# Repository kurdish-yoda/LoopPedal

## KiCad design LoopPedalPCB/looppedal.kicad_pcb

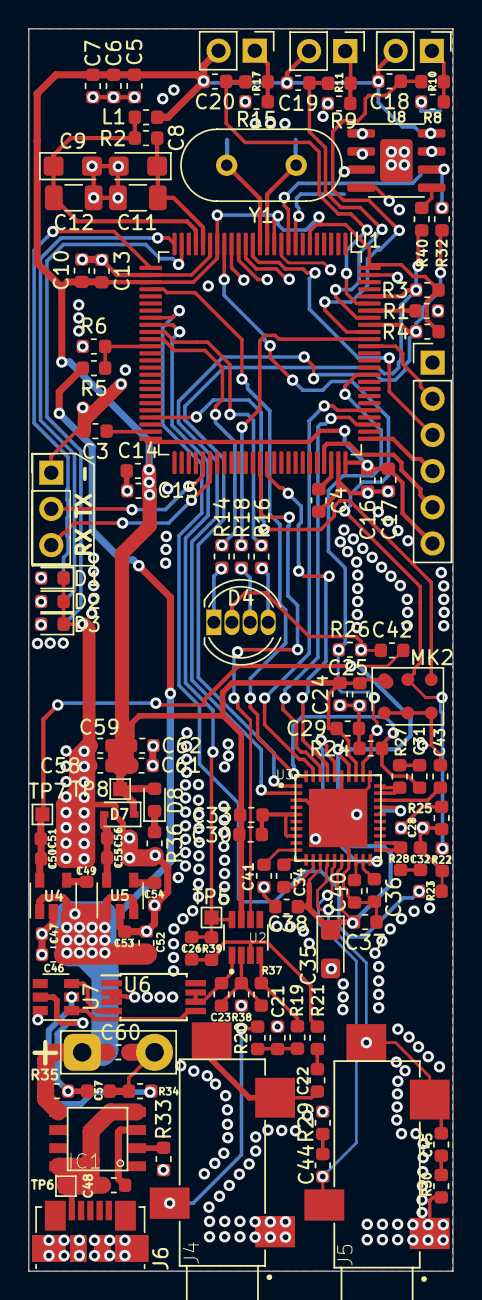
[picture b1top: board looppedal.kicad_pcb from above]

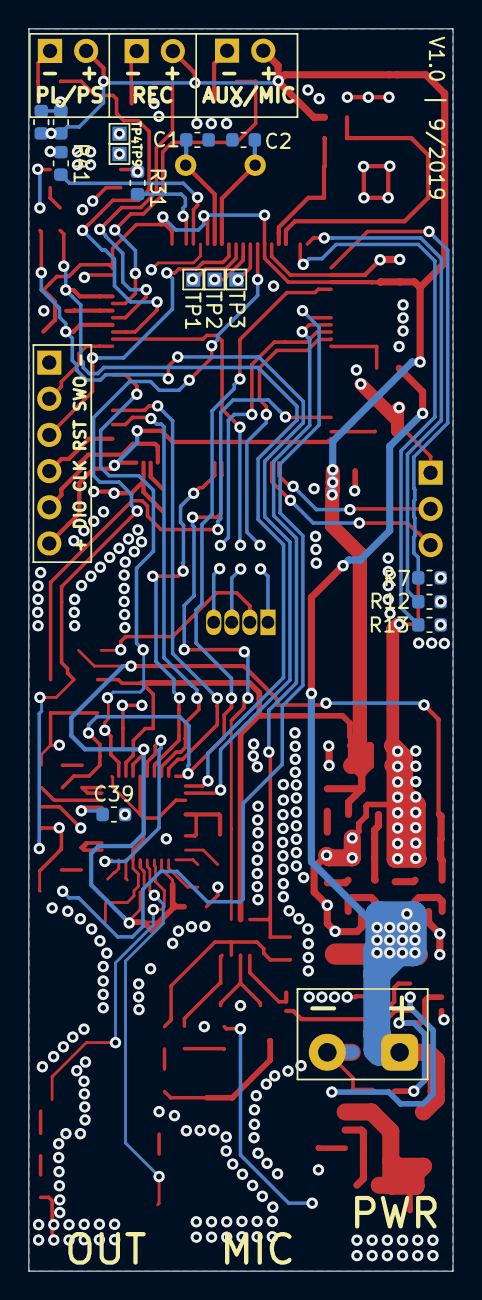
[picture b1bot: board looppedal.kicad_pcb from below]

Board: 2 copper layers, 29.8 x 87.2 mm, 140 parts (15 on the bottom side), 94 nets.

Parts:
+: Battery; TestPoint_2Pads_Pitch5.08mm_Drill1.3mm
C1, C2: 20pF; C_0603_1608Metric
C3, C4: 2.2uF; C_0603_1608Metric
C5, C6, C7, C10, C13, C14, C15, C16, C18, C19, C20, C24, C27, C28, C47, C51, C53, C56, C58, C59, C61, C62, C63: 100nF; C_0603_1608Metric
C8, C9: 1uF; CP_EIA-3216-12_Kemet-S
C11, C12: 100nF; C_1206_3216Metric
C17, C30, C31, C32, C33, C34, C36, C40, C41, C46, C50, C52, C55: 1uF; C_0603_1608Metric
C21, C25, C60: 10uF; C_0603_1608Metric
C22, C29, C37, C38, C42: 0.1uF; C_0603_1608Metric
C23: 0.01uF; C_0603_1608Metric
C26: 47pF; C_0603_1608Metric
C35: CP; CP_EIA-3216-12_Kemet-S
C39, C43: 150pF; C_0603_1608Metric
C44, C45: 0.022uF; C_0603_1608Metric
C48, C57: 0.1uF/25V; C_0603_1608Metric
C49, C54: 10nF; C_0603_1608Metric
D1, D2, D3, D8: LED; LED_0603_1608Metric
D4: LED_RCBG; LED_D5.0mm-4_RGB
D7: D_Schottky_ALT; D_SOD-323
IC1: TP4056; SOP-8
J1: SW_PLAY_PAUSE; PinHeader_1x02_P2.54mm_Vertical
J2: SW_REC; PinHeader_1x02_P2.54mm_Vertical
J3: SW_AUX_MIC; PinHeader_1x02_P2.54mm_Vertical
J4, J5: SJ-3524-SMT-PI; CUI_SJ-3524-SMT-PI
J6: USB_B_Micro; USB_Micro-B_Molex_47346-0001
J8: Conn_01x06; PinHeader_1x06_P2.54mm_Vertical
J9: DBG; PinHeader_1x03_P2.54mm_Vertical
L1: fcm; L_0603_1608Metric
MK2: MP45DT02; ST_HLGA-6_3.76x4.72mm_P1.65mm
R1, R6: 510; R_0603_1608Metric
R2: 47; R_0603_1608Metric
R3, R4: 4.7k; R_0603_1608Metric
R5: 10k; R_0603_1608Metric
R7, R12, R13, R14, R16, R18, R19, R31, R34, R36, R41: 1K; R_0603_1608Metric
R8, R9, R15, R24, R25, R37, R38: 100K; R_0603_1608Metric
R10, R11, R17, R26: 10K; R_0603_1608Metric
R20: 2K2; R_0603_1608Metric
R21: 20K; R_0603_1608Metric
R22, R33: 1.2K; R_0603_1608Metric
R23, R32, R40: 0; R_0603_1608Metric
R27, R28, R35: 100; R_0603_1608Metric
R29, R30: 51; R_0603_1608Metric
R39: 200K; R_0603_1608Metric
TP1, TP2, TP3, TP4, TP5, TP6, TP7, TP8, TP9: TestPoint; TestPoint_Pad_1.0x1.0mm
U1: STM32F407VGTx; LQFP-100_14x14mm_P0.5mm
U2: MAX4468EKAT; SOT65P280X145-8N
U3: CS43L22-CNZ; QFN50P600X600X100-41N
U4: LD3985M25R_SOT23; SOT-23-5
U5: LD3985M33R_SOT23; SOT-23-5
U6: FS8205; TSSOP-8_4.4x3mm_P0.65mm
U7: DW01; SOT-23-6
U8: M24M02-DRMN6TP; SOIC-8-1EP_3.9x4.9mm_P1.27mm_EP2.29x3mm
Y1: 8MHz; Crystal_HC49-U_Vertical

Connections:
+2V5: C35.1, C37.2, C38.2, C42.2, C50.1, C51.1, TP7.1, U3.13, U3.16, U3.34, U4.5
-BATT: +.2, C1.2, C2.2, C3.2, C4.2, C5.1, C6.1, C7.1, C8.2, C9.2, C10.1, C11.1, C12.2, C13.1, C14.1, C15.1, C16.1, C17.1, C21.1, C23.2, C24.2, C25.2, C27.1, C28.1, C29.1, C35.2, C36.2, C37.1, C38.1, C39.2, C40.2, C41.2, C42.1, C43.2, C46.2, C47.2, C48.2, C49.2, C50.2, C51.2, C52.2, C53.2, C54.2, C55.2, C56.2, C57.1, C58.2, C59.2, C60.2, C61.2, C62.2, C63.1, D1.1, D2.1, D3.1, D4.2, IC1.1, IC1.3, J4.1, J5.1, J6.5, J6.6, J8.1, J9.1, MK2.1, MK2.2, MK2.3, R1.2, R6.1, R8.1, R9.1, R15.1, R24.1, R25.2, R26.2, R29.1, R30.1, R33.1, R34.2, R36.2, R38.1, U1.10, U1.20, U1.27, U1.74, U1.99, U2.1, U3.3, U3.17, U3.31, U3.35, U3.41, U4.2, U5.2, U6.2, U6.3, U6.6, U6.7, U7.6, U8.4, U8.9
BAT_VCC: +.1, C46.1, C47.1, C52.1, C53.1, C60.1, IC1.5, R5.2, R35.1, U4.1, U4.3, U5.1, U5.3
CHRG_0: R7.2, U1.26
CHRG_1: R12.2, U1.25
CHRG_2: R13.2, U1.24
MCU_NRST: J8.3, U1.14
MCU_VBAT: C5.2, C6.2, C7.2, C10.2, C13.2, C14.2, C15.2, C16.2, C17.2, C18.2, C19.2, C20.2, C24.1, C25.1, C27.2, C29.2, C30.1, C33.1, C58.1, C59.1, C61.1, C62.1, C63.2, D7.1, D8.2, J1.2, J2.2, J3.2, J8.6, L1.1, MK2.6, R3.2, R4.2, TP8.1, U1.6, U1.11, U1.19, U1.28, U1.50, U1.75, U1.100, U2.7, U3.33, U8.8
MCU_VDDA: C9.1, C12.1, L1.2, R2.2, U1.22
MCU_VREF+: C8.1, C11.2, R2.1, U1.21
unnamed: C1.1, U1.12, Y1.1
unnamed: C2.1, U1.13, Y1.2
unnamed: C3.1, U1.49
unnamed: C4.1, U1.73
unnamed: C21.2, R19.1, R20.2
unnamed: C22.1, R21.1
unnamed: C22.2, J4.2, J4.4
unnamed: C23.1, R37.1, R38.2, U2.2
unnamed: C26.2, R21.2, R39.1, U2.3
unnamed: C28.2, C32.1, R22.2, R23.2, R25.1
unnamed: C30.2, C33.2, U3.5, U3.8
unnamed: C31.2, R27.2
unnamed: C32.2, R28.2
unnamed: C34.1, U3.12
unnamed: C34.2, U3.11
unnamed: C36.1, U3.19
unnamed: C39.1, U3.27
unnamed: C40.1, U3.18
unnamed: C41.1, U3.10
unnamed: C43.1, U3.28
unnamed: C44.1, J5.3, U3.15
unnamed: C44.2, R29.2
unnamed: C45.1, J5.2, J5.4, U3.14
unnamed: C45.2, R30.2
unnamed: C48.1, IC1.4, IC1.8, J6.1, TP6.1
unnamed: C49.1, U4.4
unnamed: C54.1, U5.4
unnamed: C55.1, C56.1, D7.2, U5.5
unnamed: C57.2, R35.2, U7.5
unnamed: D1.2, R7.1
unnamed: D2.2, R12.1
unnamed: D3.2, R13.1
unnamed: D4.1, R14.2
unnamed: D4.3, R18.2
unnamed: D4.4, R16.2
unnamed: D8.1, R36.1
unnamed: IC1.2, R33.2
unnamed: J1.1, R8.2, R10.2
unnamed: J2.1, R9.2, R11.2
unnamed: J3.1, R15.2, R17.2
unnamed: J4.3, R20.1
unnamed: R1.1, U1.94
unnamed: R19.2, R37.2, U2.4
unnamed: R27.1, U3.29, U3.30
unnamed: R28.1, U3.21, U3.22
unnamed: R31.2, U8.3
unnamed: R32.1, U8.6
unnamed: R34.1, U7.2
unnamed: R40.1, U8.5
unnamed: R41.1, U8.7
unnamed: TP1.1, U1.15
unnamed: TP2.1, U1.16
unnamed: TP3.1, U1.17
unnamed: TP4.1, U8.1
unnamed: TP9.1, U8.2
unnamed: U3.20, U3.36
unnamed: U6.4, U7.3
unnamed: U6.5, U7.1
PA4: C31.1, R24.2, U1.29, U3.40
PA13: J8.5, U1.72
PA14: J8.4, U1.76
PB2: R5.1, R6.2, U1.37
PB3: J8.2, U1.89
PB6: R4.1, R32.2, U1.92, U3.2
PB9: R3.1, R40.2, U1.96, U3.1
PB10: MK2.4, U1.47
PC3: MK2.5, R22.1, U1.18
PC4: R23.1, U1.33
PC5: C26.1, R39.2, TP5.1, U1.34, U2.8
PC6: U1.63, U2.6
PC7: U1.64, U3.37
PC10: U1.78, U3.38
PC12: U1.80, U3.39
PC14: R31.1, U1.8
PC15: R41.2, U1.9
PD4: R26.1, U1.85, U3.32
STATUS_0: R14.1, U1.36
STATUS_1: R16.1, U1.35
STATUS_2: R18.1, U1.90
SW_AUXMIC: C20.1, R17.1, U1.95
SW_PLAY_PAUSE: C18.1, R10.1, U1.91
SW_REC: C19.1, R11.1, U1.93
UART3_RX: J9.3, U1.56
UART3_TX: J9.2, U1.55

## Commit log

2020-04-27 some order
